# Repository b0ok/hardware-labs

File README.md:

# Hardware & Electronics Labs

Circuit design, PCB layout, microcontroller and FPGA work from the Computer Engineering Technology program at Sheridan College (2023).

## PCB design: Autodesk EAGLE (`eagle-pcb/`)
| Project | What it is | Images |
|---|---|---|
| **Electronic siren** (Assignment 1) | Two LM555 timers: one slowly ramps the pitch of the other to drive a speaker | [schematic](eagle-pcb/Assignment1/electronic_siren_schematic.png) |
| **PIC programmer board** (Lab 1) | PIC16F84A circuit with programming header, crystal and 5 V regulator | [schematic](eagle-pcb/Lab1/lab1_schematic.png) · [board](eagle-pcb/Lab1/lab1_board.png) |
| **Low-pass & band-pass filters** (Lab 2) | Analog filter circuits and their layouts | [LPF](eagle-pcb/TN_project/low_pass_filter_schematic.png) · [BPF](eagle-pcb/TN_project/band_pass_filter_schematic.png) |
| **LED blinker** (Week 3) | Through-hole blinker circuit | [schematic](eagle-pcb/WEEK3/blinker_schematic.png) · [board](eagle-pcb/WEEK3/blinker_board.png) |

## FPGA: VHDL (`fpga-vhdl/`)
- **`lab9_pwm.vhd`**: PWM generator for a 50 MHz FPGA board. It outputs a 2 kHz signal, and a switch toggles the duty cycle between 70% and 10%.
- **`full_adder.vhd`, `full_adder2.vhd`**: an early draft of a 4-bit ripple-carry adder (work in progress, doesn't compile as-is)

## Digital logic simulation: NI Multisim (`multisim/`)
Lab 7 decoder circuits built from 74-series logic chips and simulated in Multisim 14.1. They open in desktop Multisim or the free browser version at [multisim.com](https://www.multisim.com).
- **`74138_3-to-8_decoder.ms14`**: a 74138 decoder that turns a 3-bit binary input into one of 8 active outputs
- **`7447_bcd-to-7-segment_decoder.ms14`**: a 7447 decoder that drives a 7-segment display to show digits 0–9

<!-- Add screenshots of both circuits here. -->

## Microcontrollers: PSoC 5LP (`psoc-5lp/`)
Labs on the Cypress/Infineon CY8CKIT-059 kit, built in PSoC Creator: LED blinking (Lab 3/4) and a character LCD display (Lab 5). Each folder holds the `main.c` firmware and the project/schematic files.

## Other
- `autocad/`: 2D drafting exercises (`.dwg`, opens in [Autodesk Viewer](https://viewer.autodesk.com))
- `tinkercad/`: circuit simulations (Lab 3 and Lab 4 electric siren)

## Tools
Autodesk EAGLE · PSoC Creator 4.4 · Intel Quartus Prime · NI Multisim · AutoCAD · Tinkercad

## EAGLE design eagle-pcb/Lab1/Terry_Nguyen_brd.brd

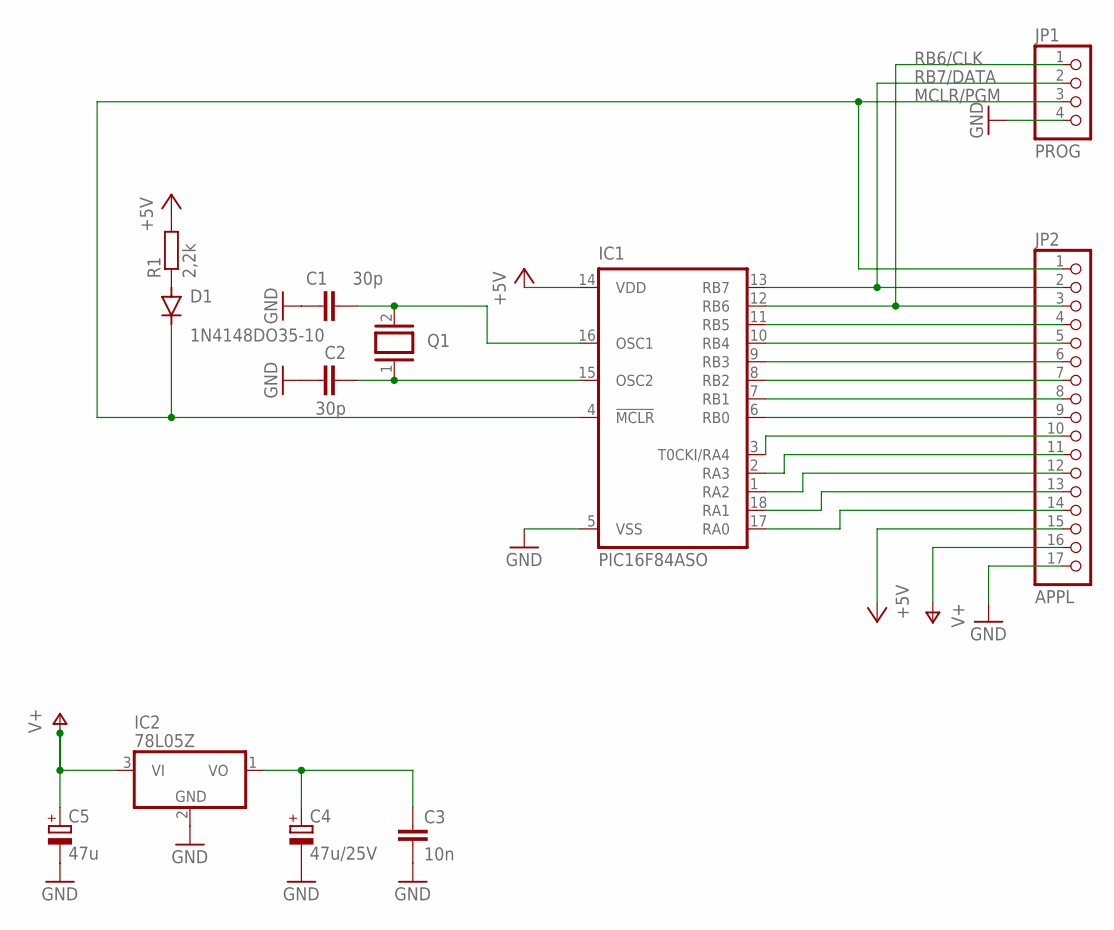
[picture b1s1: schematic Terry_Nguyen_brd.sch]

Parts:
C1, C2: 30p; C1206
C3: 10n; C025-025X050
C4: 47u/25V; TAP5-45
C5: 47u; TAP5-45
D1: 1N4148DO35-10; DO35-10
IC1: PIC16F84ASO; SO-18W
IC2: 78L05Z; TO92
JP1: PROG; 1X04
JP2: APPL; 1X17
Q1: XTAL/S; QS
R1: 2,2k; R1206

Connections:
+5V: IC1.14 (VDD), JP2.15, R1.2
GND: C1.1, C2.1, C3.2, C4.-, C5.-, IC1.5 (VSS), IC2.2 (GND), JP1.4, JP2.17
MCLR/PGM: D1.C, IC1.4 (!MCLR), JP1.3, JP2.1
unnamed: C3.1, C4.+, IC2.1 (VO)
unnamed: C1.2, IC1.16 (OSC1), Q1.2
unnamed: C2.2, IC1.15 (OSC2), Q1.1
unnamed: D1.A, R1.1
RA0: IC1.17 (RA0), JP2.14
RA1: IC1.18 (RA1), JP2.13
RA2: IC1.1 (RA2), JP2.12
RA3: IC1.2 (RA3), JP2.11
RA4: IC1.3 (T0CKI/RA4), JP2.10
RB0: IC1.6 (RB0), JP2.9
RB1: IC1.7 (RB1), JP2.8
RB2: IC1.8 (RB2), JP2.7
RB3: IC1.9 (RB3), JP2.6
RB4: IC1.10 (RB4), JP2.5
RB5: IC1.11 (RB5), JP2.4
RB6/CLK: IC1.12 (RB6), JP1.1, JP2.3
RB7/DATA: IC1.13 (RB7), JP1.2, JP2.2
V+: C5.+, IC2.3 (VI), JP2.16

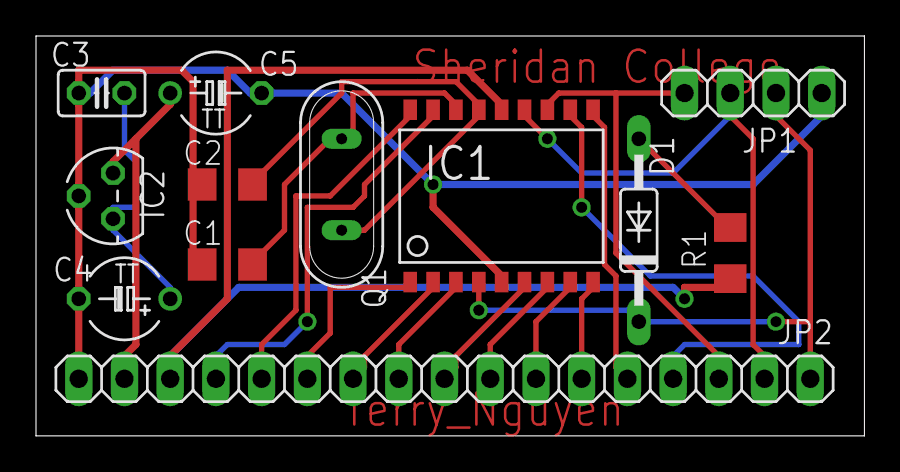
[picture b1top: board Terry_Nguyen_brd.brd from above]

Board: 2 copper layers, 46.0 x 22.2 mm, 12 parts (0 on the bottom side), 21 nets.

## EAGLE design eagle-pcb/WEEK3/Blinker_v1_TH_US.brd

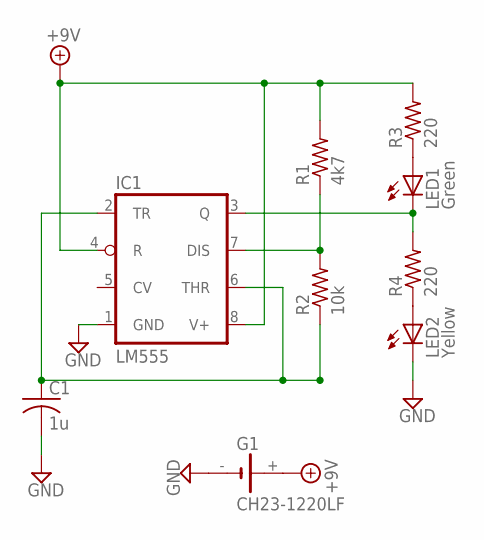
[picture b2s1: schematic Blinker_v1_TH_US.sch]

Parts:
C1: 1u; C025-025X050
G1: CH23-1220LF
IC1: LM555; DIL08
LED1: Green; LED5MM
LED2: Yellow; LED5MM
R1: 4k7; 0204/7
R2: 10k; 0204/7
R3, R4: 220; 0204/7

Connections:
+9V: G1.+, IC1.4 (R), IC1.8 (V+), R1.2, R3.2
GND: C1.2, G1.-, IC1.1 (GND), LED2.K (C)
unnamed: LED1.A, R3.1
unnamed: IC1.3 (Q), LED1.K (C), R4.2
unnamed: LED2.A, R4.1
unnamed: IC1.7 (DIS), R1.1, R2.2
unnamed: C1.1, IC1.2 (TR), IC1.6 (THR), R2.1

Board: 2 copper layers, 9 parts (0 on the bottom side), 7 nets, no tracks yet.

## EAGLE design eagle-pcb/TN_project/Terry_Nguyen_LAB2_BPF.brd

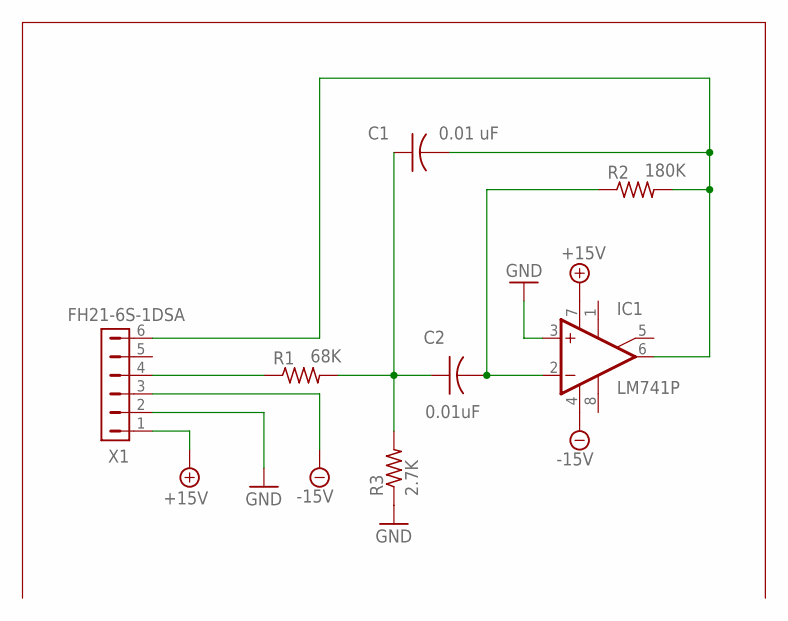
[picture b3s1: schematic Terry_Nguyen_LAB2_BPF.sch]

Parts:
C1: 0.01 uF; C050-025X075
C2: 0.01uF; C050-025X075
IC1: LM741P; DIL08
R1: 68K; 0207/10
R2: 180K; 0207/10
R3: 2.7K; 0207/10
X1: FH21-6S-1DSA

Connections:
+15V: IC1.7 (V+), X1.1
-15V: IC1.4 (V-), X1.3
GND: IC1.3 (+IN), R3.1, X1.2
unnamed: R1.1, X1.4
unnamed: C1.1, C2.1, R1.2, R3.2
unnamed: C2.2, IC1.2 (-IN), R2.1
unnamed: C1.2, IC1.6 (OUT), R2.2, X1.6

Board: 2 copper layers, 7 parts (0 on the bottom side), 7 nets, no tracks yet.
